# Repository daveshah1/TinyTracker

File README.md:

# TinyTracker
The plan is to create a tiny (<5g) tracker for low-cost, lightweight balloon experiments.

Currently no electronics have been built, but an initial design has been made using KiCad. This is untested and likely has some mistakes. It features:

 * M10748 GPS
 * SX1276 based LoRa radio with TCXO (for ultimate performace with very low data rates)
 * STM32F048 MCU
 * MS5637 temperature/pressure sensor
 * CAT24M01 EEPROM for logging
 
It is designed to run off a small lithium polymer battery such as [PRT-00731](https://www.sparkfun.com/products/731) which, depending on logging and transmission interval, should give a battery life of over 10 hours.

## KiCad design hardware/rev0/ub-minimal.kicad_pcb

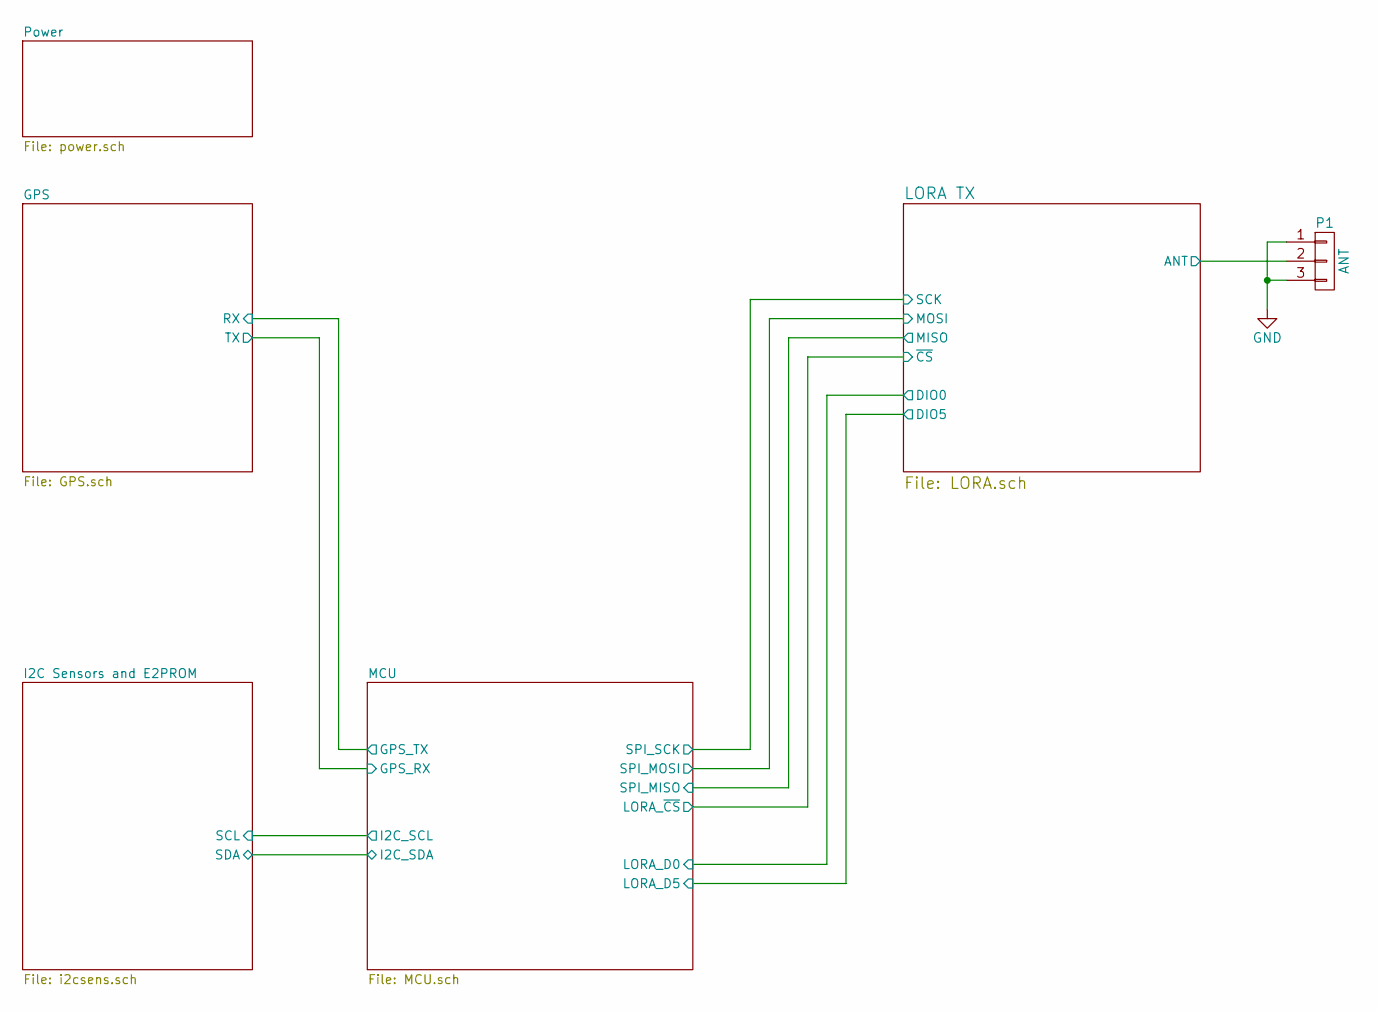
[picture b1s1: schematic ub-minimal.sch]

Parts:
P1: ANT; ANT_50ohm

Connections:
/LORA TX/ANT: P1.2; also elsewhere on the board
GND: P1.1, P1.3; also elsewhere on the board

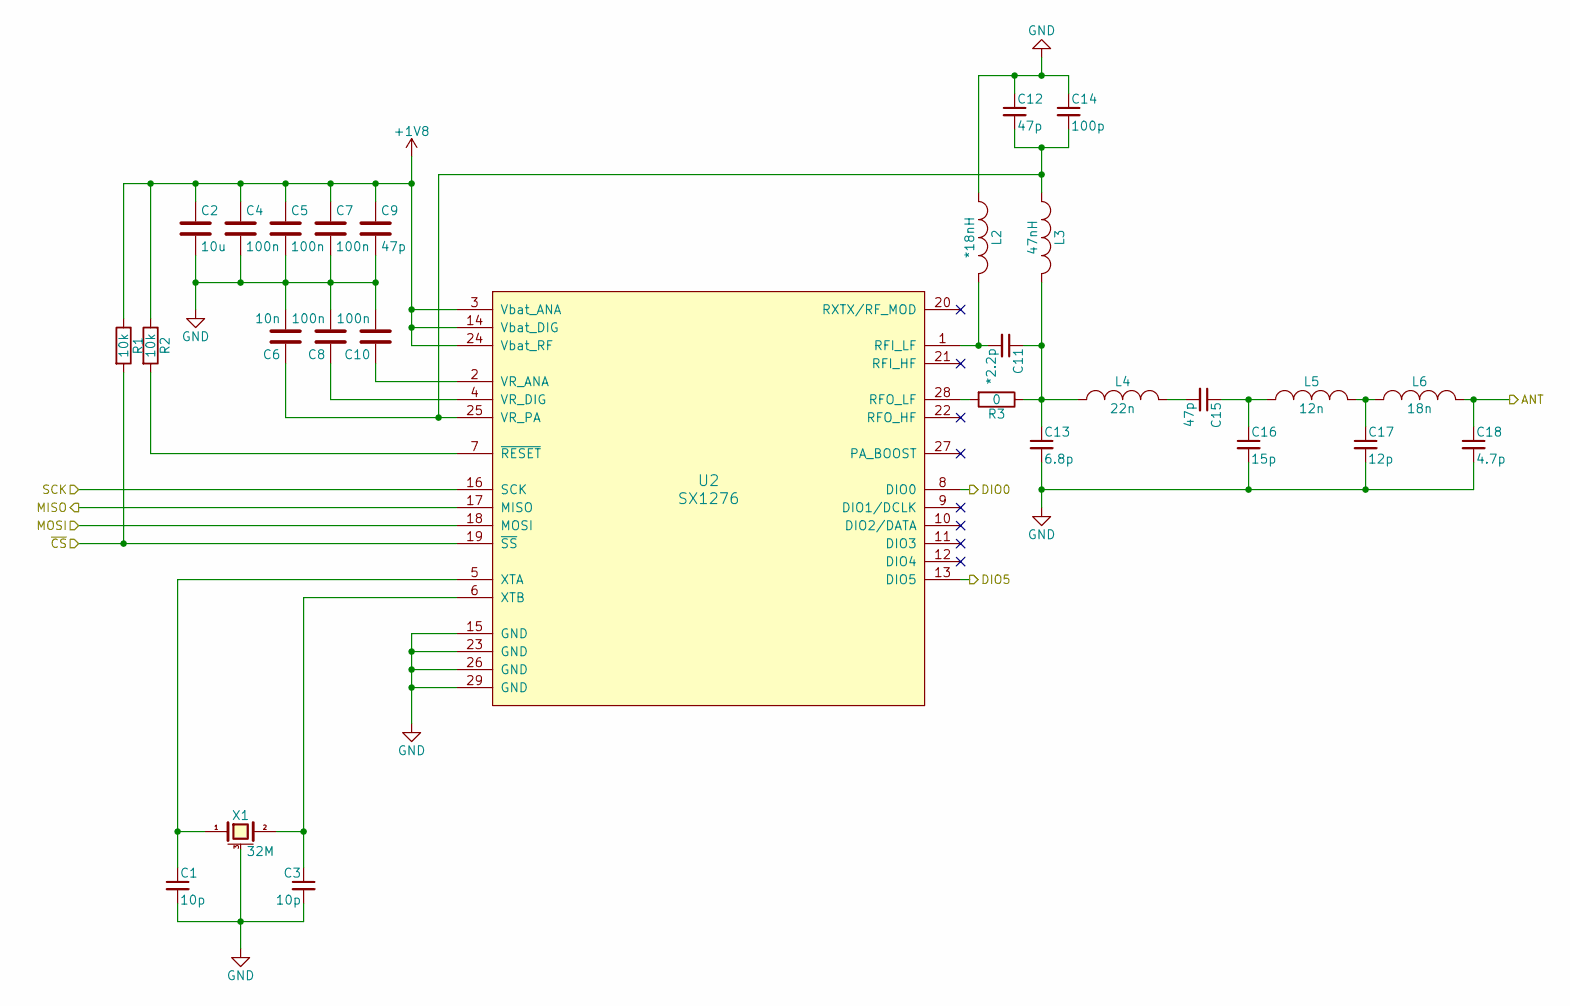
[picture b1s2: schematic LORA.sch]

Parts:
C1, C3: 10p; C_0402
C2: 10u; C_0805
C4, C5, C7, C8, C10: 100n; C_0402
C6: 10n; C_0402
C9, C12, C15: 47p; C_0402
C11: *2.2p; C_0402
C13: 6.8p; C_0402
C14: 100p; C_0402
C16: 15p; C_0402
C17: 12p; C_0402
C18: 4.7p; C_0402
L2: *18nH; R_0402
L3: 47nH; R_0402
L4: 22n; R_0402
L5: 12n; R_0402
L6: 18n; R_0402
R1, R2: 10k; R_0402
R3: 0; R_0402
U2: SX1276; QFP_28_0.65
X1: 32M; XTAL-2x2.5

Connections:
+1V8: C2.1, C4.1, C5.1, C7.1, C9.1, R1.1, R2.1, U2.3 (Vbat_ANA), U2.14 (Vbat_DIG), U2.24 (Vbat_RF); also elsewhere on the board
/LORA TX/ANT: C18.1, L6.2; also elsewhere on the board
/LORA TX/DIO0: U2.8 (DIO0); also elsewhere on the board
/LORA TX/DIO5: U2.13 (DIO5); also elsewhere on the board
/LORA TX/MISO: U2.17 (MISO); also elsewhere on the board
/LORA TX/MOSI: U2.18 (MOSI); also elsewhere on the board
/LORA TX/SCK: U2.16 (SCK); also elsewhere on the board
/MCU/LORA_~CS: R1.2, U2.19 (~SS); also elsewhere on the board
GND: C1.2, C2.2, C3.2, C4.2, C5.2, C6.2, C7.2, C8.2, C9.2, C10.2, C12.1, C13.2, C14.1, C16.2, C17.2, C18.2, L2.1, U2.15 (GND), U2.23 (GND), U2.26 (GND), U2.29 (GND), X1.3 (case); also elsewhere on the board
unnamed: C1.1, U2.5 (XTA), X1.1
unnamed: C3.1, U2.6 (XTB), X1.2
unnamed: C8.1, U2.4 (VR_DIG)
unnamed: C10.1, U2.2 (VR_ANA)
unnamed: C11.1, C13.1, L3.2, L4.1, R3.1
unnamed: C11.2, L2.2, U2.1 (RFI_LF)
unnamed: C6.1, C12.2, C14.2, L3.1, U2.25 (VR_PA)
unnamed: C15.1, C16.1, L5.1
unnamed: C15.2, L4.2
unnamed: C17.1, L5.2, L6.1
unnamed: R2.2, U2.7 (~RESET)
unnamed: R3.2, U2.28 (RFO_LF)

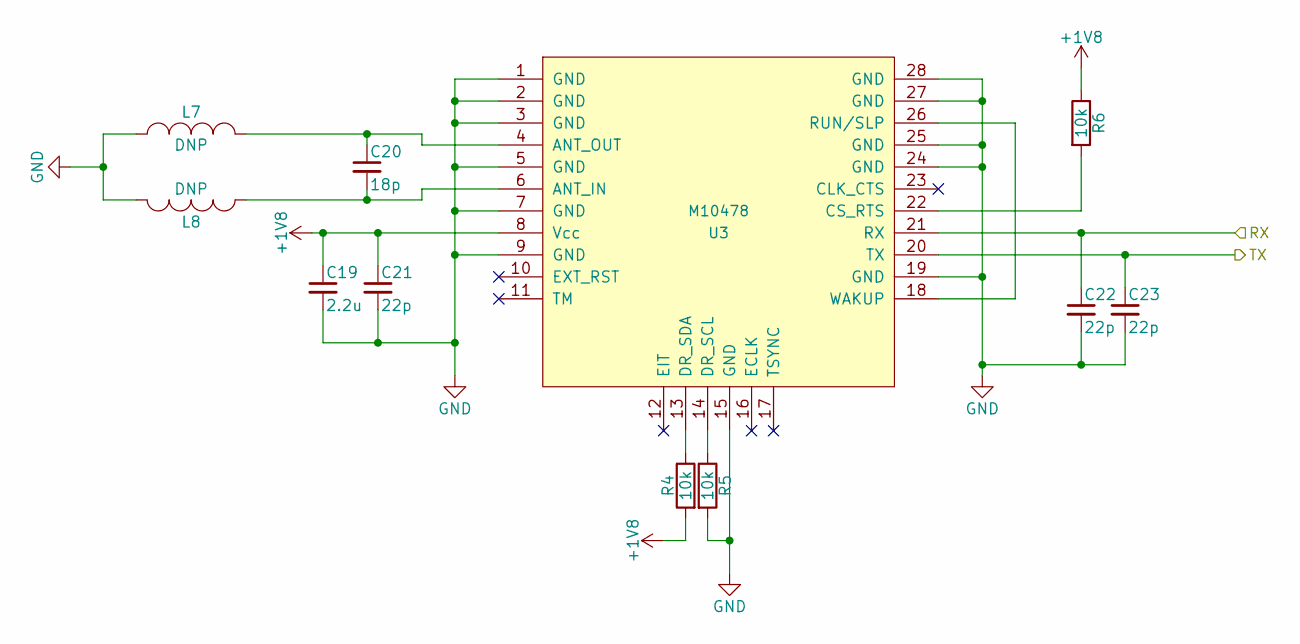
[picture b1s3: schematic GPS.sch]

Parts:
C19: 2.2u; C_0603
C20: 18p; C_0402
C21, C22, C23: 22p; C_0402
L7, L8: DNP; R_0402
R4, R5, R6: 10k; R_0402
U3: M10478; M10748

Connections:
+1V8: C19.1, C21.1, R4.2, R6.1, U3.8 (Vcc); also elsewhere on the board
/MCU/GPS_RX: C23.1, U3.20 (TX); also elsewhere on the board
/MCU/GPS_TX: C22.1, U3.21 (RX); also elsewhere on the board
GND: C19.2, C21.2, C22.2, C23.2, L7.1, L8.1, R5.2, U3.1 (GND), U3.2 (GND), U3.3 (GND), U3.5 (GND), U3.7 (GND), U3.9 (GND), U3.15 (GND), U3.19 (GND), U3.24 (GND), U3.25 (GND), U3.27 (GND), U3.28 (GND); also elsewhere on the board
unnamed: C20.1, L7.2, U3.4 (ANT_OUT)
unnamed: C20.2, L8.2, U3.6 (ANT_IN)
unnamed: R4.1, U3.13 (DR_SDA)
unnamed: R5.1, U3.14 (DR_SCL)
unnamed: R6.2, U3.22 (CS_RTS)
unnamed: U3.18 (WAKUP), U3.26 (RUN/SLP)

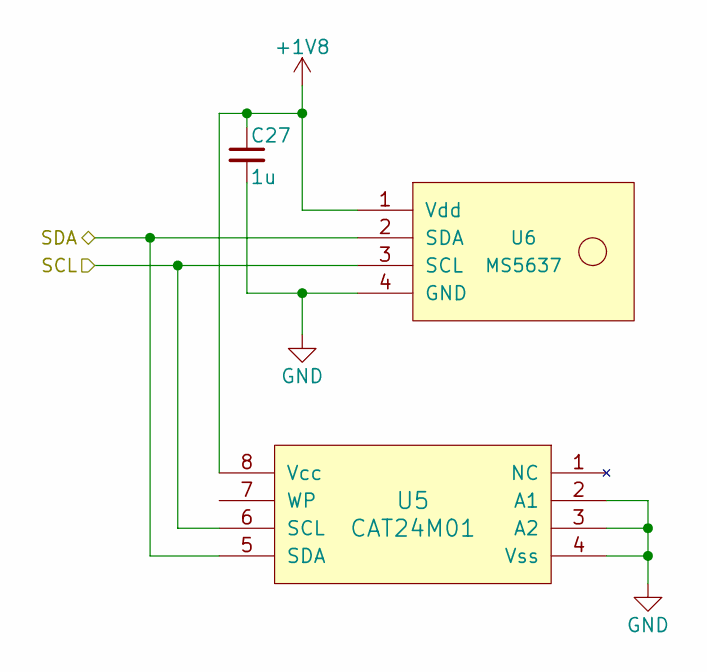
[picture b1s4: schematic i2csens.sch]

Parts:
C27: 1u; C_0603
U5: CAT24M01; UDFN8
U6: MS5637

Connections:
+1V8: C27.1, U5.8 (Vcc), U6.1 (Vdd); also elsewhere on the board
/MCU/I2C_SCL: U5.6 (SCL), U6.3 (SCL); also elsewhere on the board
/MCU/I2C_SDA: U5.5 (SDA), U6.2 (SDA); also elsewhere on the board
GND: C27.2, U5.2 (A1), U5.3 (A2), U5.4 (Vss), U6.4 (GND); also elsewhere on the board

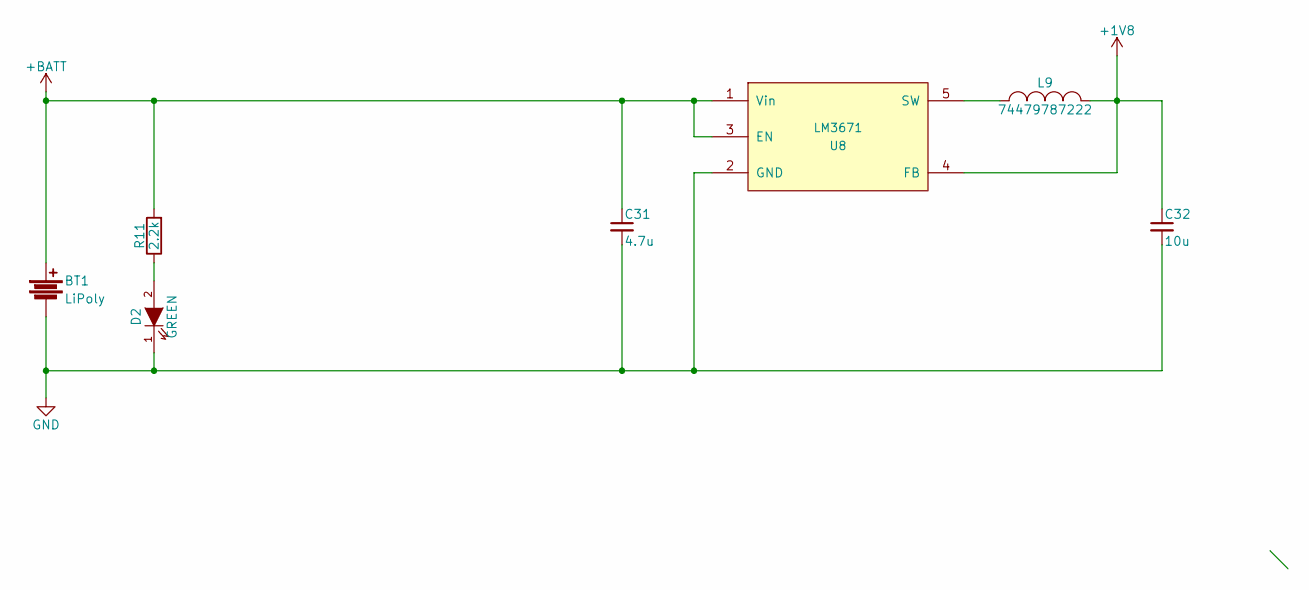
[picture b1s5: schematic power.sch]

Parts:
BT1: LiPoly; S2B-PH-SM4-TB
C31: 4.7u; C_0805
C32: 10u; C_0805
D2: GREEN; LED-0603
L9: 74479787222; Neosid_Inductor_SM-NE29_SMD1008
R11: 2.2k; R_0402
U8: LM3671; SOT-23-5

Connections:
+1V8: C32.1, L9.2, U8.4 (FB); also elsewhere on the board
+BATT: BT1.1, C31.1, R11.2, U8.1 (Vin), U8.3 (EN)
GND: BT1.2, C31.2, C32.2, D2.1 (K), U8.2 (GND); also elsewhere on the board
unnamed: D2.2 (A), R11.1
unnamed: L9.1, U8.5 (SW)

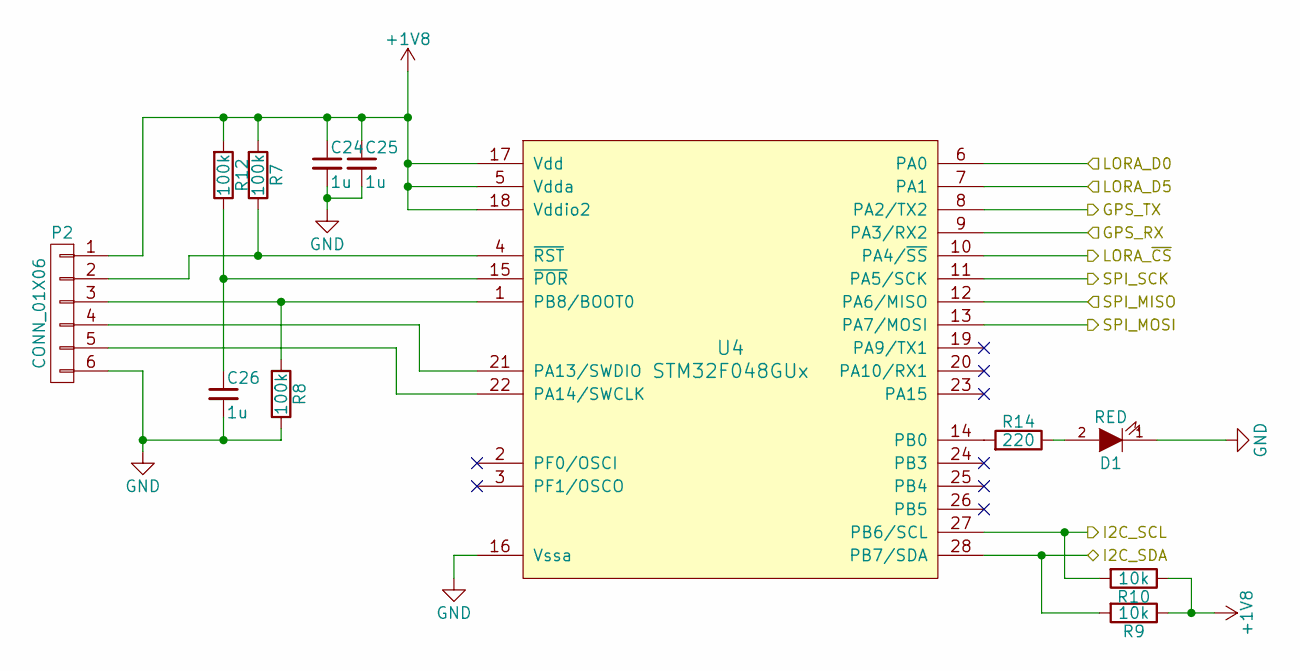
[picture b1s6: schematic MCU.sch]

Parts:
C24, C25, C26: 1u; C_0603
D1: RED; LED-0603
P2: CONN_01X06; 6-1.27mm
R7, R8, R12: 100k; R_0402
R9, R10: 10k; R_0402
R14: 220; R_0402
U4: STM32F048GUx; UFQFPN28

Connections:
+1V8: C24.1, C25.1, P2.1, R7.2, R9.1, R10.1, R12.2, U4.5 (Vdda), U4.17 (Vdd), U4.18 (Vddio2); also elsewhere on the board
/LORA TX/DIO0: U4.6 (PA0); also elsewhere on the board
/LORA TX/DIO5: U4.7 (PA1); also elsewhere on the board
/LORA TX/MISO: U4.12 (PA6/MISO); also elsewhere on the board
/LORA TX/MOSI: U4.13 (PA7/MOSI); also elsewhere on the board
/LORA TX/SCK: U4.11 (PA5/SCK); also elsewhere on the board
/MCU/GPS_RX: U4.9 (PA3/RX2); also elsewhere on the board
/MCU/GPS_TX: U4.8 (PA2/TX2); also elsewhere on the board
/MCU/I2C_SCL: R10.2, U4.27 (PB6/SCL); also elsewhere on the board
/MCU/I2C_SDA: R9.2, U4.28 (PB7/SDA); also elsewhere on the board
/MCU/LORA_~CS: U4.10 (PA4/~SS); also elsewhere on the board
GND: C24.2, C25.2, C26.2, D1.1 (K), P2.6, R8.1, U4.16 (Vssa); also elsewhere on the board
unnamed: C26.1, R12.1, U4.15 (~POR)
unnamed: D1.2 (A), R14.1
unnamed: P2.2, R7.1, U4.4 (~RST)
unnamed: P2.3, R8.2, U4.1 (PB8/BOOT0)
unnamed: P2.4, U4.21 (PA13/SWDIO)
unnamed: P2.5, U4.22 (PA14/SWCLK)
unnamed: R14.2, U4.14 (PB0)

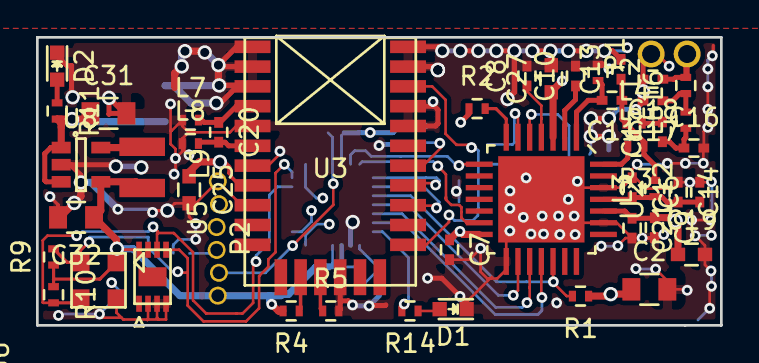
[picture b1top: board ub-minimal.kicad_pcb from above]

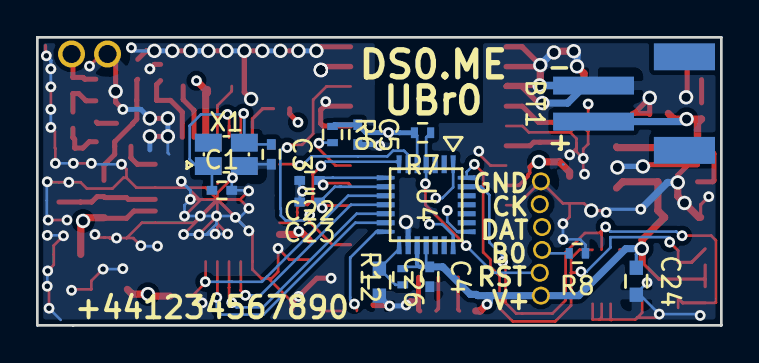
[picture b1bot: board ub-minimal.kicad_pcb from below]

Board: 4 copper layers, 38.0 x 16.0 mm, 62 parts (15 on the bottom side), 41 nets.

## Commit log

2015-11-20 Add project information
2015-11-20 Add hardware revision 0
    Currently unchecked & untested
2016-01-26 Replace TCXO with XTAL
    Planned TCXO became obsolete and hard to source, high quality XTAL
    should be good enough with possible temperature compensation in
    software.
2016-01-27 DRC alterations, generate gerbers
2016-01-28 Various fixes and tweaks
2016-01-31 Add FB network
    Allow system to run off 2V if needed
